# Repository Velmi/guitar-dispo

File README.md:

# guitar-dispo
Digital signal processing on a STM32 Nucleo Board

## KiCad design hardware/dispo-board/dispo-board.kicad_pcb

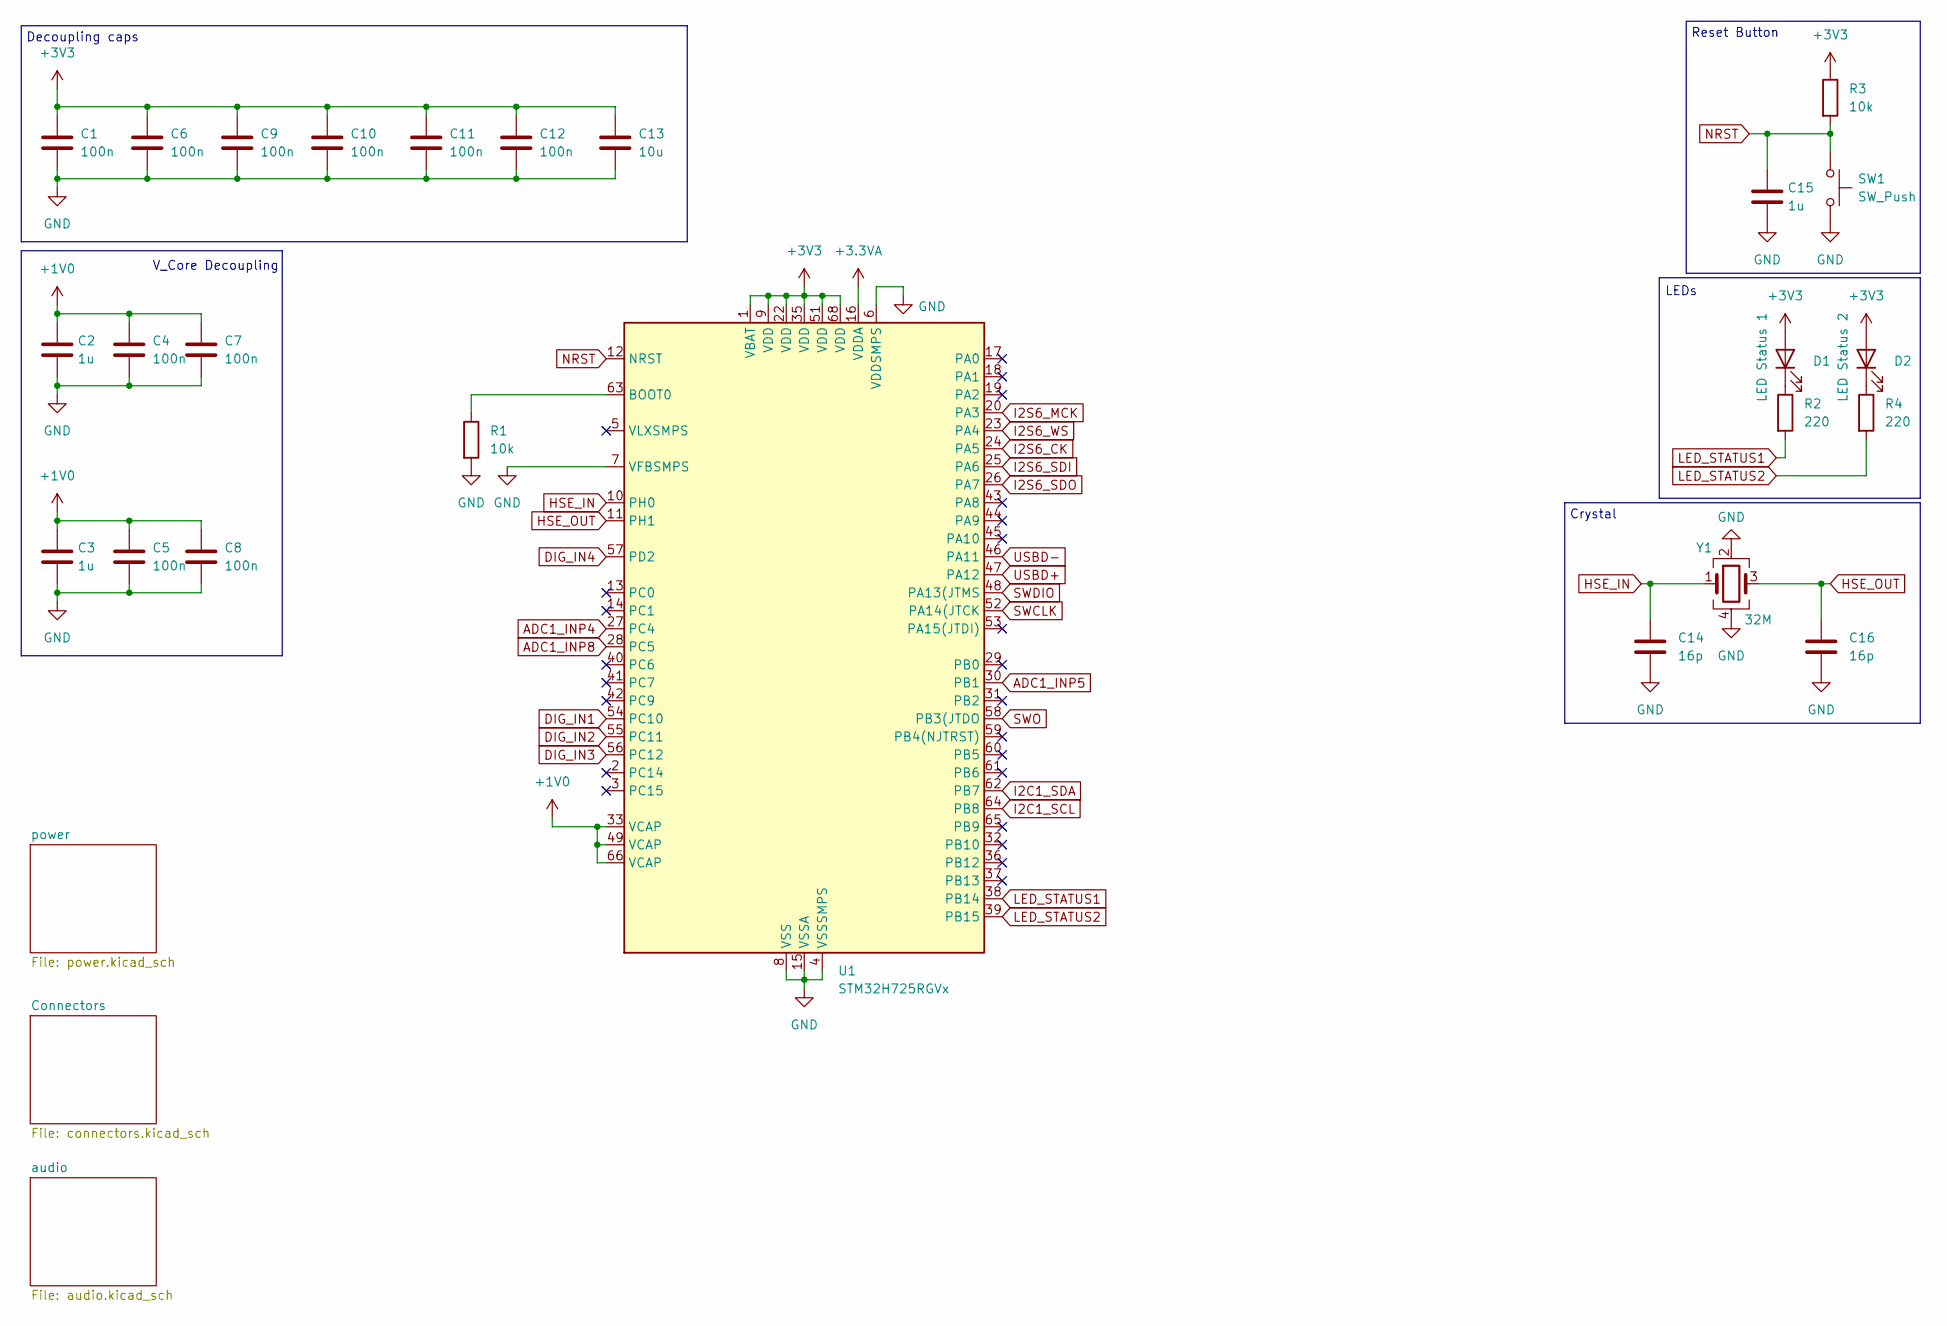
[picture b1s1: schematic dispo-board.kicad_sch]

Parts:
C1, C4, C5, C6, C7, C8, C9, C10, C11, C12: 100n; C_0402_1005Metric; MOUSER_NR 963-MCASL105SB7104KF
C2, C3, C15: 1u; C_0402_1005Metric; MOUSER_NR 963-LMK105BJ105MVHF
C13: 10u; C_0603_1608Metric; MOUSER_NR 963-LMK107BBJ106MALT
C14, C16: 16p; C_0402_1005Metric; MOUSER_NR 81-GCM1555C1H160FA6D
D1: LED Status 1; LED_0603_1608Metric; MOUSER_NR 645-598-8N80-107F
D2: LED Status 2; LED_0603_1608Metric; MOUSER_NR 645-598-8N80-107F
R1, R3: 10k; R_0402_1005Metric; MOUSER_NR 652-CR0402-JW-103GLF
R2, R4: 220; R_0402_1005Metric; MOUSER_NR 652-CR0402FX-2200GLF
SW1: SW_Push; SW_Push_1P1T_NO_CK_KSC7xxJ; MOUSER_NR 506-FSM2JSMAATR
U1: STM32H725RGVx; QFN-68-1EP_8x8mm_P0.4mm_EP6.4x6.4mm
Y1: 32M; Crystal_SMD_2016-4Pin_2.0x1.6mm; MOUSER_NR 815-11W32-8D1XT

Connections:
+1V0: C2.1, C3.1, C4.1, C5.1, C7.1, C8.1, U1.33 (VCAP), U1.49 (VCAP), U1.66 (VCAP); also elsewhere on the board
+3.3VA: U1.16 (VDDA); also elsewhere on the board
+3V3: C1.1, C6.1, C9.1, C10.1, C11.1, C12.1, C13.1, D1.2 (A), D2.2 (A), R3.1, U1.1 (VBAT), U1.9 (VDD), U1.22 (VDD), U1.35 (VDD), U1.51 (VDD), U1.68 (VDD); also elsewhere on the board
ADC1_INP4: U1.27 (PC4); also elsewhere on the board
ADC1_INP5: U1.30 (PB1); also elsewhere on the board
ADC1_INP8: U1.28 (PC5); also elsewhere on the board
DIG_IN1: U1.54 (PC10); also elsewhere on the board
DIG_IN2: U1.55 (PC11); also elsewhere on the board
DIG_IN3: U1.56 (PC12); also elsewhere on the board
DIG_IN4: U1.57 (PD2); also elsewhere on the board
GND: C1.2, C2.2, C3.2, C4.2, C5.2, C6.2, C7.2, C8.2, C9.2, C10.2, C11.2, C12.2, C13.2, C14.2, C15.2, C16.2, R1.2, SW1.2, U1.4 (VSSSMPS), U1.6 (VDDSMPS), U1.7 (VFBSMPS), U1.8 (VSS), U1.15 (VSSA), U1.21 (VSS), U1.34 (VSS), U1.50 (VSS), U1.67 (VSS), U1.69 (VSS), Y1.2, Y1.4; also elsewhere on the board
HSE_IN: C14.1, U1.10 (PH0), Y1.1
HSE_OUT: C16.1, U1.11 (PH1), Y1.3
I2C1_SCL: U1.64 (PB8); also elsewhere on the board
I2C1_SDA: U1.62 (PB7); also elsewhere on the board
I2S6_CK: U1.24 (PA5); also elsewhere on the board
I2S6_MCK: U1.20 (PA3); also elsewhere on the board
I2S6_SDI: U1.25 (PA6); also elsewhere on the board
I2S6_SDO: U1.26 (PA7); also elsewhere on the board
I2S6_WS: U1.23 (PA4); also elsewhere on the board
LED_STATUS1: R2.2, U1.38 (PB14)
LED_STATUS2: R4.2, U1.39 (PB15)
NRST: C15.1, R3.2, SW1.1, U1.12 (NRST); also elsewhere on the board
unnamed: D1.1 (K), R2.1
unnamed: D2.1 (K), R4.1
unnamed: R1.1, U1.63 (BOOT0)
SWCLK: U1.52 (PA14(JTCK); also elsewhere on the board
SWDIO: U1.48 (PA13(JTMS); also elsewhere on the board
SWO: U1.58 (PB3(JTDO); also elsewhere on the board
USBD+: U1.47 (PA12); also elsewhere on the board
USBD-: U1.46 (PA11); also elsewhere on the board

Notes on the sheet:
V_Core Decoupling
Decoupling caps
Crystal
Reset Button
LEDs

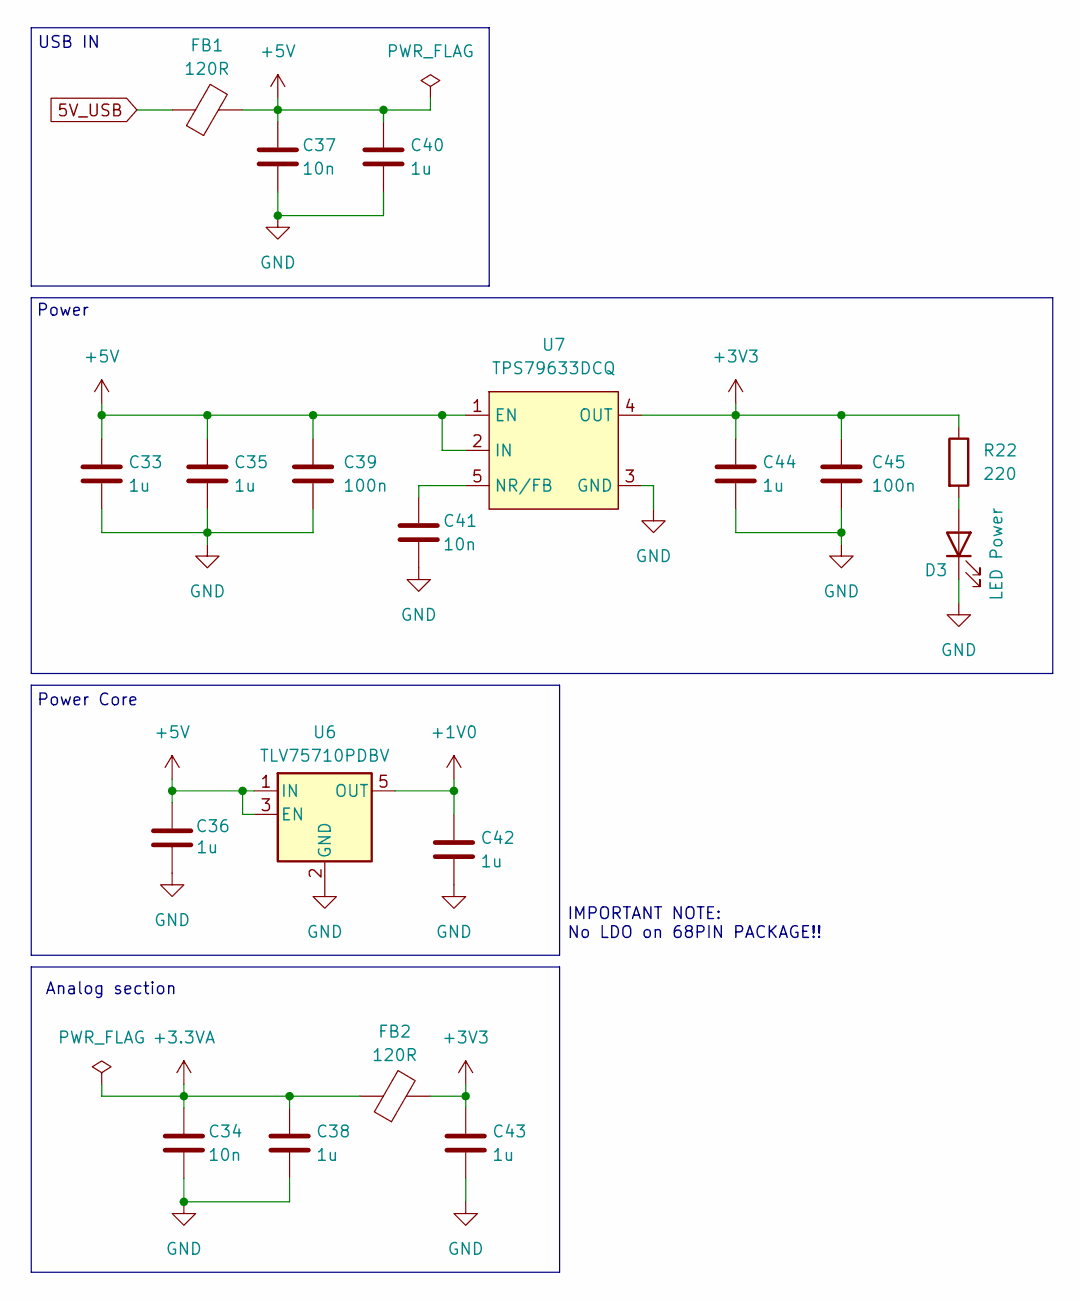
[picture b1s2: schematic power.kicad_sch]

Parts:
C33, C35, C36, C38, C40, C42, C43, C44: 1u; C_0402_1005Metric; MOUSER_NR 963-LMK105BJ105MVHF
C34, C37, C41: 10n; C_0402_1005Metric; MOUSER_NR 81-GRM155R61A103KA1D
C39, C45: 100n; C_0402_1005Metric; MOUSER_NR 963-MCASL105SB7104KF
D3: LED Power; LED_0603_1608Metric; MOUSER_NR 645-598-8N80-107F
FB1, FB2: 120R; R_0402_1005Metric; MOUSER_NR 81-BLM15PX121SH1D
R22: 220; R_0402_1005Metric; MOUSER_NR 652-CR0402FX-2200GLF
U6: TLV75710PDBV; SOT-23-5
U7: TPS79633DCQ; SOT-223-6; MOUSER_NO 595-TPS79633DCQ

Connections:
5V_USB: FB1.1; also elsewhere on the board
+1V0: C42.1, U6.5 (OUT); also elsewhere on the board
+3.3VA: C34.1, C38.1, FB2.1; also elsewhere on the board
+3V3: C43.1, C44.1, C45.1, FB2.2, R22.1, U7.4 (OUT); also elsewhere on the board
+5V: C33.1, C35.1, C36.1, C37.1, C39.1, C40.1, FB1.2, U6.1 (IN), U6.3 (EN), U7.1 (EN), U7.2 (IN)
GND: C33.2, C34.2, C35.2, C36.2, C37.2, C38.2, C39.2, C40.2, C41.2, C42.2, C43.2, C44.2, C45.2, D3.1 (K), U6.2 (GND), U7.3 (GND), U7.6 (GND); also elsewhere on the board
unnamed: D3.2 (A), R22.2
unnamed: C41.1, U7.5 (NR/FB)

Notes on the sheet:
USB IN
Power
Power Core
IMPORTANT NOTE: No LDO on 68PIN PACKAGE!!
Analog section

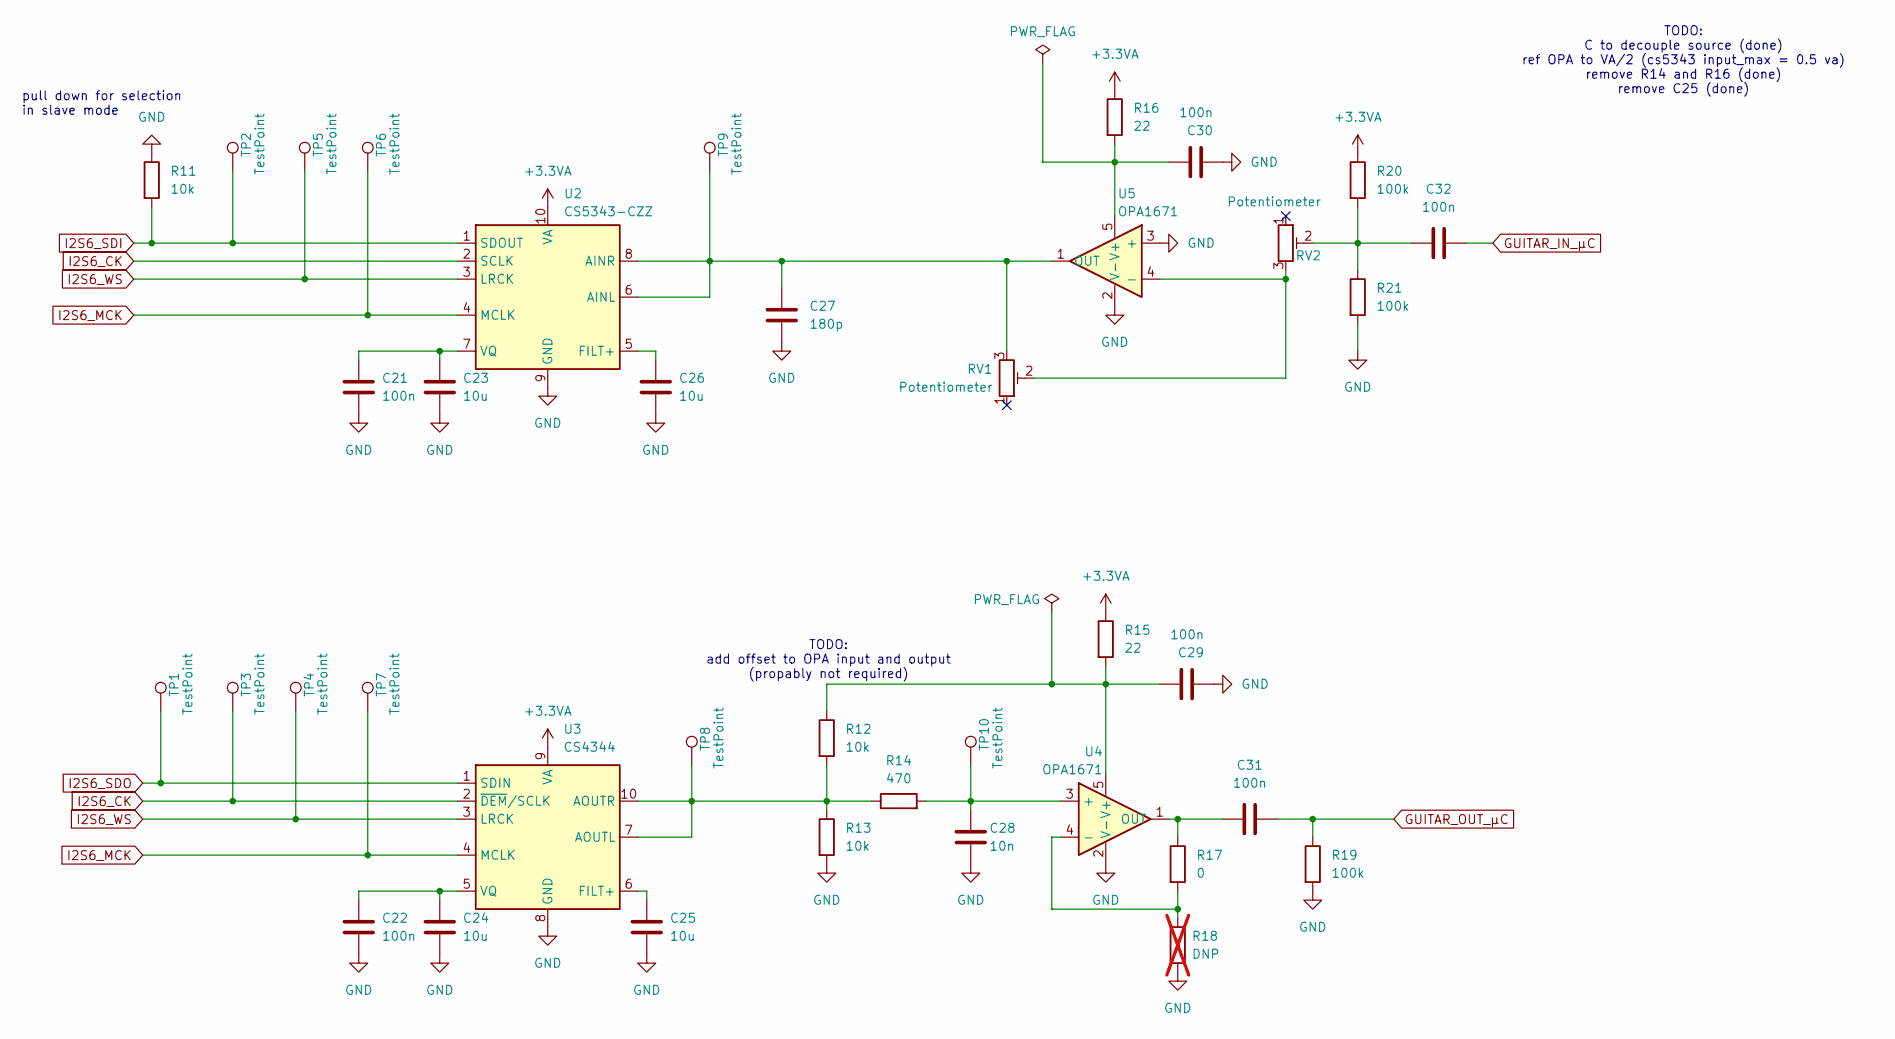
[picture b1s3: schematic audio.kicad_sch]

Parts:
C21, C22, C29, C30: 100n; C_0402_1005Metric; MOUSER_NR 963-MCASL105SB7104KF
C23, C24, C25, C26: 10u; C_0603_1608Metric; MOUSER_NR 963-LMK107BBJ106MALT
C27: 180p; C_0402_1005Metric; MOUSER_NR 81-GCM1555C1H181JA6D
C28: 10n; C_0402_1005Metric; MOUSER_NR 81-GRM155R61A103KA1D
C31, C32: 100n; C_1210_3225Metric; MOUSER_NR 667-ECH-U1C104JX5
R11, R13: 10k; R_0402_1005Metric; MOUSER_NR 652-CR0402-JW-103GLF
R12: 10k; R_0402_1005Metric; MOUSER_NR 71-CRCW040210K0FKEDC
R14: 470; R_0402_1005Metric; MOUSER_NR 667-ERA-2VEB4700X
R15, R16: 22; R_0603_1608Metric; MOUSER_NR 652-CHP0603QJW-220E
R17: 0; R_0402_1005Metric; MOUSER_NR 710-560112110001
R18: DNP; R_0402_1005Metric; not fitted
R19, R20, R21: 100k; R_0402_1005Metric; MOUSER_NR 652-CR0402JW-104GLF
RV1, RV2: Potentiometer; Potentiometer_Bourns_3224W_Vertical; MOUSER_NR 652-3224W-1-503E
TP1, TP2, TP3, TP4, TP5, TP6, TP7, TP8, TP9, TP10: TestPoint; TestPoint_Pad_D1.5mm
U2: CS5343-CZZ; TSSOP-10_3x3mm_P0.5mm; MOUSER_NR 777-CS5343-CZZ
U3: CS4344; TSSOP-10_3x3mm_P0.5mm; MOUSER_NR 777-CS4344-CZZR
U4, U5: OPA1671; SOT-23-5; MOUSER_NR 595-OPA1671IDBVT

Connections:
+3.3VA: R15.1, R16.1, R20.1, U2.10 (VA), U3.9 (VA); also elsewhere on the board
GND: C21.2, C22.2, C23.2, C24.2, C25.2, C26.2, C27.2, C28.2, C29.2, C30.2, R11.1, R13.2, R18.2, R19.2, R21.2, U2.9 (GND), U3.8 (GND), U4.2 (V-), U5.2 (V-), U5.3 (+); also elsewhere on the board
GUITAR_IN_µC: C32.2; also elsewhere on the board
GUITAR_OUT_µC: C31.2, R19.1; also elsewhere on the board
I2S6_CK: TP3.1, U2.2 (SCLK), U3.2 (~DEM/SCLK); also elsewhere on the board
I2S6_MCK: TP6.1, TP7.1, U2.4 (MCLK), U3.4 (MCLK); also elsewhere on the board
I2S6_SDI: R11.2, TP2.1, U2.1 (SDOUT); also elsewhere on the board
I2S6_SDO: TP1.1, U3.1 (SDIN); also elsewhere on the board
I2S6_WS: TP4.1, TP5.1, U2.3 (LRCK), U3.3 (LRCK); also elsewhere on the board
unnamed: C32.1, R20.2, R21.1, RV2.2
unnamed: C27.1, RV1.3, TP9.1, U2.6 (AINL), U2.8 (AINR), U5.1 (OUT)
unnamed: C26.1, U2.5 (FILT+)
unnamed: C21.1, C23.1, U2.7 (VQ)
unnamed: R12.2, R13.1, R14.1, TP8.1, U3.7 (AOUTL), U3.10 (AOUTR)
unnamed: C25.1, U3.6 (FILT+)
unnamed: C22.1, C24.1, U3.5 (VQ)
unnamed: C28.1, R14.2, TP10.1, U4.3 (+)
unnamed: R17.2, R18.1, U4.4 (-)
unnamed: C31.1, R17.1, U4.1 (OUT)
unnamed: C29.1, R12.1, R15.2, U4.5 (V+)
unnamed: RV1.2, RV2.3, U5.4 (-)
unnamed: C30.1, R16.2, U5.5 (V+)

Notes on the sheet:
TODO: C to decouple source (done) ref OPA to VA/2 (cs5343 input_max = 0.5 va) remove R14 and R16 (done) remove C25 (done)
pull down for selection in slave mode
TODO: add offset to OPA input and output (propably not required)

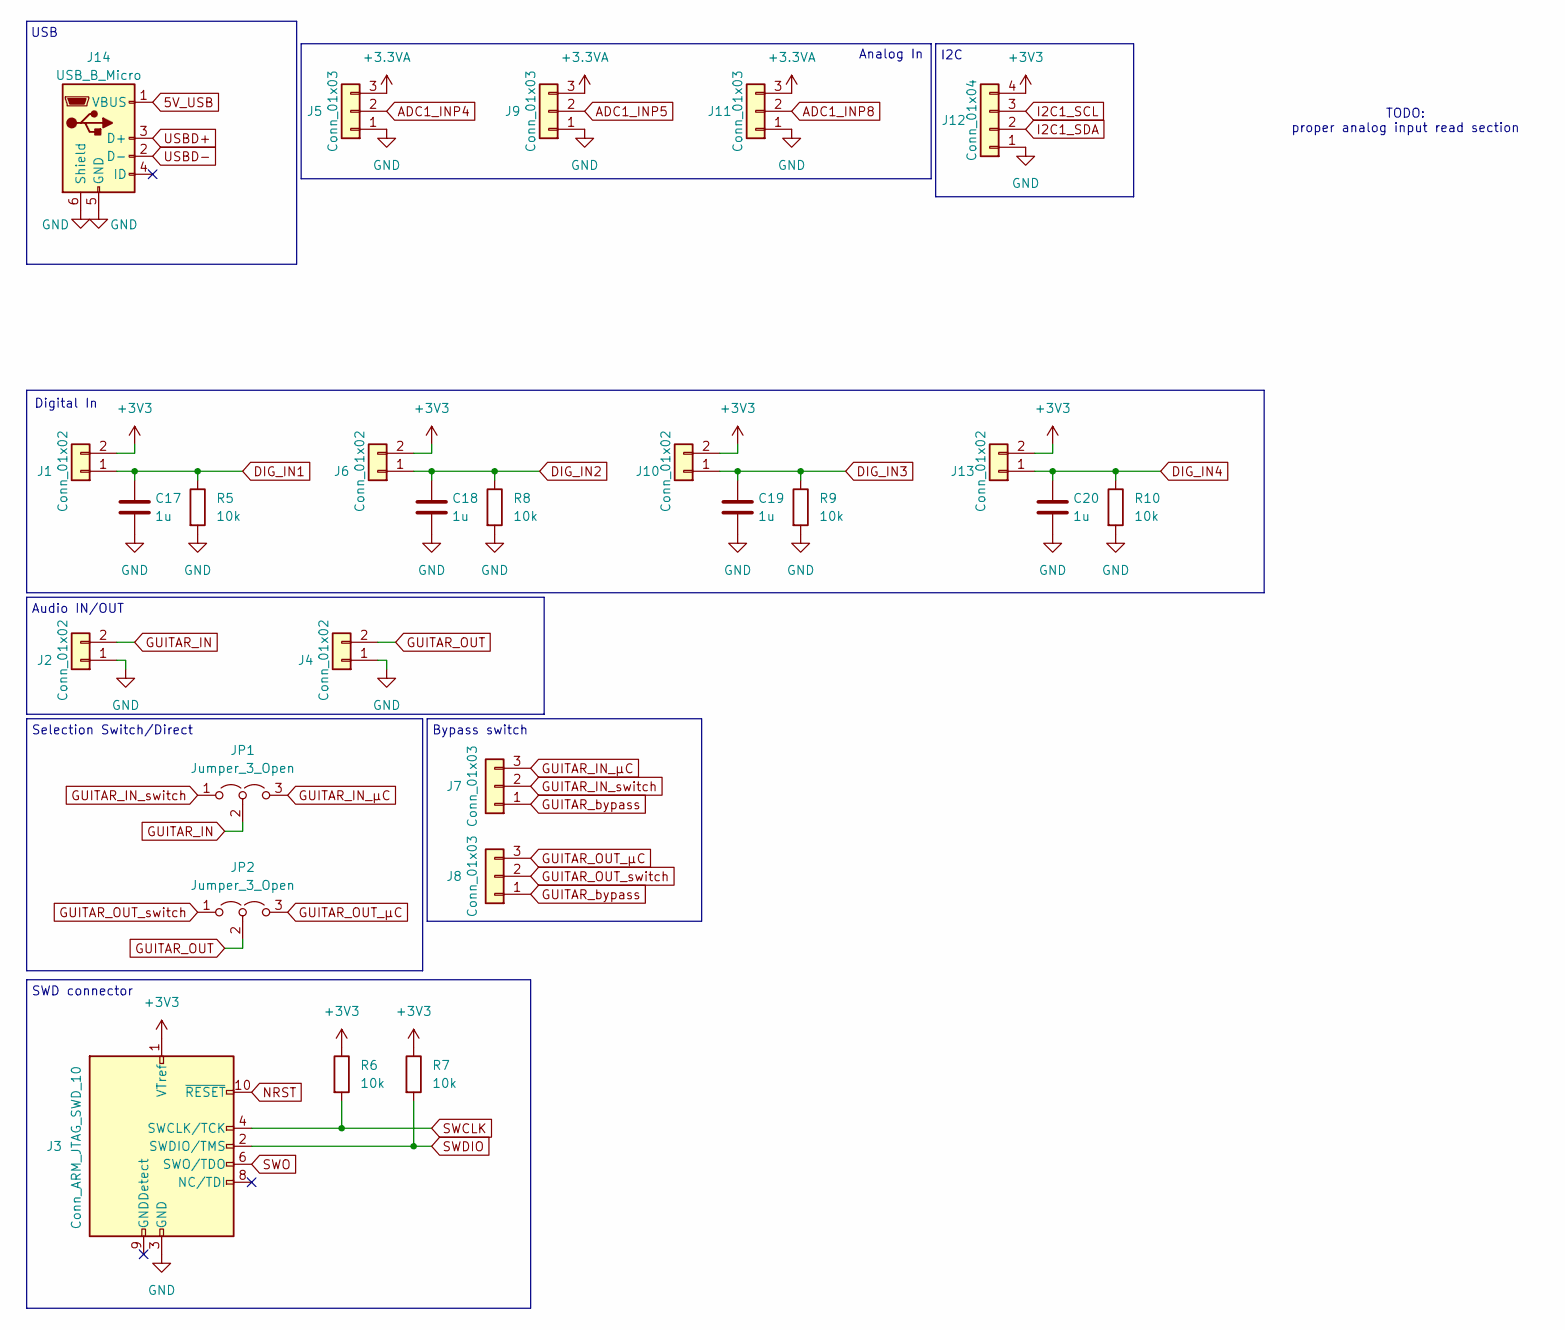
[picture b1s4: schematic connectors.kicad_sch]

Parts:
C17, C18, C19, C20: 1u; C_0402_1005Metric; MOUSER_NR 963-LMK105BJ105MVHF
J1, J2, J4, J6, J10, J13: Conn_01x02; solder_pad_1x02_D3.5mm
J3: Conn_ARM_JTAG_SWD_10; PinHeader_2x05_P1.27mm_Vertical; MOUSER_NR 474-PRT-15362
J5, J7, J8, J9, J11: Conn_01x03; solder_pad_1x03_D3.5mm
J12: Conn_01x04; PinHeader_1x04_P2.54mm_Vertical
J14: USB_B_Micro; USB_Micro-B_Molex_47346-0001; MOUSER_NR 538-47346-1001
JP1, JP2: Jumper_3_Open; PinHeader_1x03_P2.54mm_Vertical
R5, R6, R7, R8, R9, R10: 10k; R_0402_1005Metric; MOUSER_NR 652-CR0402-JW-103GLF

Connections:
5V_USB: J14.1 (VBUS); also elsewhere on the board
+3.3VA: J5.3, J9.3, J11.3; also elsewhere on the board
+3V3: J1.2, J3.1 (VTref), J6.2, J10.2, J12.4, J13.2, R6.1, R7.1; also elsewhere on the board
ADC1_INP4: J5.2; also elsewhere on the board
ADC1_INP5: J9.2; also elsewhere on the board
ADC1_INP8: J11.2; also elsewhere on the board
DIG_IN1: C17.1, J1.1, R5.1; also elsewhere on the board
DIG_IN2: C18.1, J6.1, R8.1; also elsewhere on the board
DIG_IN3: C19.1, J10.1, R9.1; also elsewhere on the board
DIG_IN4: C20.1, J13.1, R10.1; also elsewhere on the board
GND: C17.2, C18.2, C19.2, C20.2, J2.1, J3.3 (GND), J3.5 (GND), J4.1, J5.1, J9.1, J11.1, J12.1, J14.5 (GND), J14.6 (Shield), R5.2, R8.2, R9.2, R10.2; also elsewhere on the board
GUITAR_IN: J2.2, JP1.2 (C)
GUITAR_IN_switch: J7.2, JP1.1 (A)
GUITAR_IN_µC: J7.3, JP1.3 (B); also elsewhere on the board
GUITAR_OUT: J4.2, JP2.2 (C)
GUITAR_OUT_switch: J8.2, JP2.1 (A)
GUITAR_OUT_µC: J8.3, JP2.3 (B); also elsewhere on the board
GUITAR_bypass: J7.1, J8.1
I2C1_SCL: J12.3; also elsewhere on the board
I2C1_SDA: J12.2; also elsewhere on the board
NRST: J3.10 (~RESET); also elsewhere on the board
SWCLK: J3.4 (SWCLK/TCK), R6.2; also elsewhere on the board
SWDIO: J3.2 (SWDIO/TMS), R7.2; also elsewhere on the board
SWO: J3.6 (SWO/TDO); also elsewhere on the board
USBD+: J14.3 (D+); also elsewhere on the board
USBD-: J14.2 (D-); also elsewhere on the board

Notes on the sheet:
Audio IN/OUT
Selection Switch/Direct
I2C
Analog In
USB
Bypass switch
SWD connector
TODO: proper analog input read section
Digital In

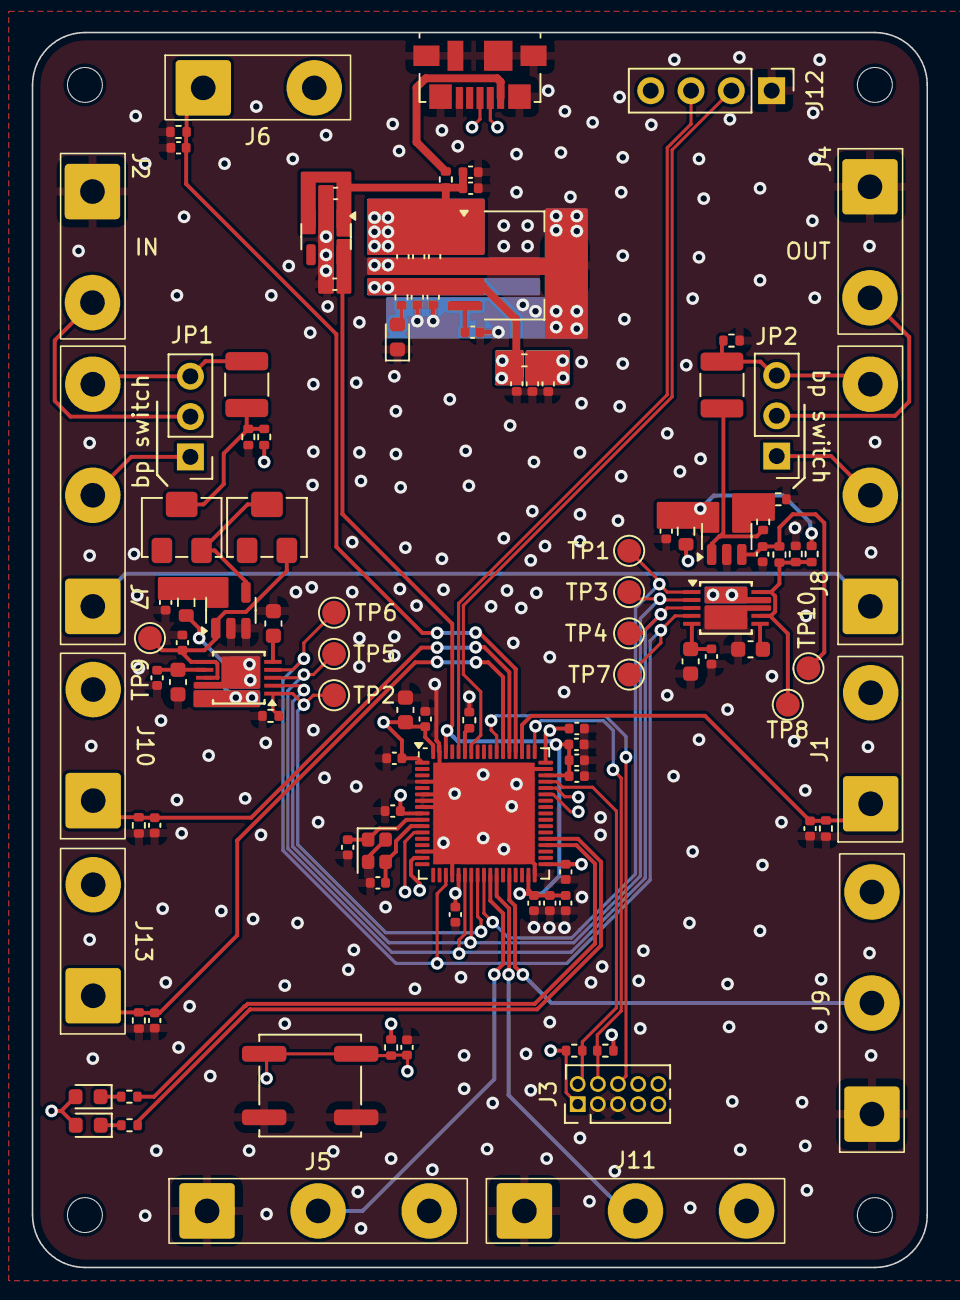
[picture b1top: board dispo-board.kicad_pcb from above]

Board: 4 copper layers, 56.4 x 77.8 mm, 109 parts (0 on the bottom side), 55 nets.

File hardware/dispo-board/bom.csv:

"Reference","Value","Datasheet","Footprint","Qty","DNP"
"C1,C4,C5,C6,C7,C8,C9,C10,C11,C12,C21,C22,C29,C30,C31,C32,C39,C45","100n","~","Capacitor_SMD:C_0402_1005Metric,Capacitor_SMD:C_1210_3225Metric","18",""
"C2,C3,C15,C17,C18,C19,C20,C33,C35,C36,C38,C40,C42,C43,C44","1u","~","Capacitor_SMD:C_0402_1005Metric","15",""
"C13,C23,C24,C25,C26","10u","~","Capacitor_SMD:C_0603_1608Metric","5",""
"C14,C16","16p","~","Capacitor_SMD:C_0402_1005Metric","2",""
"C27","180p","~","Capacitor_SMD:C_0402_1005Metric","1",""
"C28,C34,C37,C41","10n","~","Capacitor_SMD:C_0402_1005Metric","4",""
"D1","LED Status 1","~","LED_SMD:LED_0603_1608Metric","1",""
"D2","LED Status 2","~","LED_SMD:LED_0603_1608Metric","1",""
"D3","LED Power","~","LED_SMD:LED_0603_1608Metric","1",""
"FB1,FB2","120R","~","Resistor_SMD:R_0402_1005Metric","2",""
"J1,J2,J4,J6,J10,J13","Conn_01x02","~","MyFootprints:solder_pad_1x02_D3.5mm","6",""
"J3","Conn_ARM_JTAG_SWD_10","http://infocenter.arm.com/help/topic/com.arm.doc.ddi0314h/DD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","Connector_PinHeader_1.27mm:PinHeader_2x05_P1.27mm_Vertical","1",""
"J5,J7,J8,J9,J11","Conn_01x03","~","MyFootprints:solder_pad_1x03_D3.5mm","5",""
"J12","Conn_01x04","~","Connector_PinHeader_2.54mm:PinHeader_1x04_P2.54mm_Vertical","1",""
"J14","USB_B_Micro","~","Connector_USB:USB_Micro-B_Molex_47346-0001","1",""
"JP1,JP2","Jumper_3_Open","~","Connector_PinHeader_2.54mm:PinHeader_1x03_P2.54mm_Vertical","2",""
"R1,R3,R5,R6,R7,R8,R9,R10,R11,R12,R13","10k","~","Resistor_SMD:R_0402_1005Metric","11",""
"R2,R4,R22","220","~","Resistor_SMD:R_0402_1005Metric","3",""
"R14","470","~","Resistor_SMD:R_0402_1005Metric","1",""
"R15,R16","22","~","Resistor_SMD:R_0603_1608Metric","2",""
"R17","0","~","Resistor_SMD:R_0402_1005Metric","1",""
"R19,R20,R21","100k","~","Resistor_SMD:R_0402_1005Metric","3",""
"RV1,RV2","Potentiometer","~","Potentiometer_SMD:Potentiometer_Bourns_3224W_Vertical","2",""
"SW1","SW_Push","~","Button_Switch_SMD:SW_Push_1P1T_NO_CK_KSC7xxJ","1",""
"TP1,TP2,TP3,TP4,TP5,TP6,TP7,TP8,TP9,TP10","TestPoint","~","TestPoint:TestPoint_Pad_D1.5mm","10",""
"U1","STM32H725RGVx","https://www.st.com/resource/en/datasheet/stm32h725rg.pdf","Package_DFN_QFN:QFN-68-1EP_8x8mm_P0.4mm_EP6.4x6.4mm","1",""
"U2","CS5343-CZZ","https://statics.cirrus.com/pubs/proDatasheet/CS5343-44_F5.pdf","Package_SO:TSSOP-10_3x3mm_P0.5mm","1",""
"U3","CS4344","https://statics.cirrus.com/pubs/proDatasheet/CS4344-45-48_F2.pdf","Package_SO:TSSOP-10_3x3mm_P0.5mm","1",""
"U4,U5","OPA1671","https://www.ti.com/lit/ds/symlink/opa1671.pdf?ts=17124005870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","Package_TO_SOT_SMD:SOT-23-5","2",""
"U6","TLV75710PDBV","https://www.ti.com/lit/ds/symlink/tlv757p.pdf","Package_TO_SOT_SMD:SOT-23-5","1",""
"U7","TPS79633DCQ","https://www.ti.com/general/docs/suppproductinfo.tsp?distId=2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","Package_TO_SOT_SMD:SOT-223-6","1",""
"Y1","32M","~","Crystal:Crystal_SMD_2016-4Pin_2.0x1.6mm","1",""

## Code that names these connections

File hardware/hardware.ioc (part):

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Mcu.Name=STM32H725RGVx
Mcu.Package=VFQFPN68
Mcu.UserName=STM32H725RGVx
PA11.Mode=Device_Only_FS
PA11.Signal=USB_OTG_HS_DM
PA12.Mode=Device_Only_FS
PA12.Signal=USB_OTG_HS_DP
PA13(JTMS/SWDIO).Mode=Trace_Asynchronous_SW
PA13(JTMS/SWDIO).Signal=DEBUG_JTMS-SWDIO
PA14(JTCK/SWCLK).Mode=Trace_Asynchronous_SW
PA14(JTCK/SWCLK).Signal=DEBUG_JTCK-SWCLK
PA3.Mode=Master_Clock_Activated
PA3.Signal=I2S6_MCK
PA4.Mode=Full_Duplex_Master
PA4.Signal=I2S6_WS
PA5.Mode=Full_Duplex_Master
PA5.Signal=I2S6_CK
PA6.Mode=Full_Duplex_Master
PA6.Signal=I2S6_SDI
PA7.Mode=Full_Duplex_Master
PA7.Signal=I2S6_SDO
PA8.Mode=Activate_SOF_FS
PA8.Signal=USB_OTG_HS_SOF
PB1.Signal=ADCx_INP5
PB13.Signal=GPIO_Output
PB14.Signal=GPIO_Output
PB15.Signal=GPIO_Output
PB3(JTDO/TRACESWO).Mode=Trace_Asynchronous_SW
PB3(JTDO/TRACESWO).Signal=DEBUG_JTDO-SWO
PB7.Mode=I2C
PB7.Signal=I2C1_SDA
PB8.Mode=I2C
PB8.Signal=I2C1_SCL
PC10.Signal=GPIO_Input
PC11.Signal=GPIO_Input
PC12.Signal=GPIO_Input
PC4.Signal=ADCx_INP4
PC5.Signal=ADCx_INP8
PD2.Signal=GPIO_Input
PH0-OSC_IN.Mode=HSE-External-Oscillator
PH0-OSC_IN.Signal=RCC_OSC_IN
PH1-OSC_OUT.Mode=HSE-External-Oscillator
PH1-OSC_OUT.Signal=RCC_OSC_OUT
RCC.HSE_VALUE=32000000
RCC.SYSCLKFreq_VALUE=400000000
RCC.SYSCLKSource=RCC_SYSCLKSOURCE_PLLCLK
board=custom

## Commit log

2023-07-23 started with intro, basics and concept
2023-07-25 FIR, IIR, double buffering
2023-07-27 added STM32CubeIDE project
2023-07-27 moved report into doc
2023-07-27 deleted old folder
2023-07-27 little changes, added implementation
2023-07-27 little changes
2023-08-01 added CLI, added bandpass filter, added lowpass filter to poti-ADC
2023-08-06 added kicad project
2023-08-21 blabla
2023-11-22 power, quarz, switch to internal USB
2024-03-10 add decoupling caps, connectors, audio, minor corrections in report
2024-03-21 added analog frontend
2024-03-24 maybe final schematic?
2024-03-29 added debugger, corrected erc errors
2024-03-30 added footprints and mouser nrs
2024-04-07 few changes supply op amp, anaolg input and output, updated footprints and mouser nrs
2024-04-14 added missing footprint
2024-04-24 updated footprints, pcb
2024-04-30 pcb layout drc check passed
2024-04-30 corrected vias and placements
2024-05-02 updated pcb, changed via sizes, drc check, ...
2024-06-27 pcb and parts ordered like this
2024-07-07 added ibom
2024-07-08 error in schematic: no LDO on package, must use SMPS, switched to kicad 8, modified filter script
2024-08-20 added pcb
2024-09-11 basic software, bandpass fir filter, added notes to hardware modifications
2024-09-11 modified gitignore
2024-09-13 fir and iir filter working at right frequencies
2024-09-13 doc working on implementation
2024-09-13 scripts for filterdesign working
2024-09-13 audio nucleo changes, kicad notes for hardware issues
2024-09-13 minor fix
2024-09-13 added freertos
2024-09-15 abgabe version
2024-09-15 abgabe
2024-10-03 ready for presentation
2024-11-02 new abgabe version
2024-11-02 changed gitignore, new pdf
2025-06-01 bypassing filter when pedal completely released
2025-07-06 schematic should be ready, changed parts, ...
2025-07-27 deleted nucleo board files, schematic ready?, changed to usb c
2025-08-03 changed to old ldo
2025-08-03 corrected ldo schematic
2025-08-03 annotate schmetic
2025-11-11 shorted board
2025-11-23 routed i2s and analog and digital pins, rst button and debug connector not finished
2025-12-26 routing almost finished, need GND plane
2026-01-17 changed again to micro usb, resolved spacing issues
2026-01-18 everything connected, ready?
2026-01-21 changed text sizes, some other stuff
2026-01-21 added some text, minor changes, should be ready for production
2026-01-25 added manifacturing files
2026-01-31 ordered pcb and stuff
2026-02-16 bom and stuff
2026-03-21 cleanup
2026-03-28 added delay line via ringbuffer
2026-04-12 added flanger, removed ringbuffer from all implementations, explicit delay line, need better solution for input/output of processing blocks
2026-05-03 added effectschain, changed flanger to chorus
2026-05-03 updated vulnarable packages
